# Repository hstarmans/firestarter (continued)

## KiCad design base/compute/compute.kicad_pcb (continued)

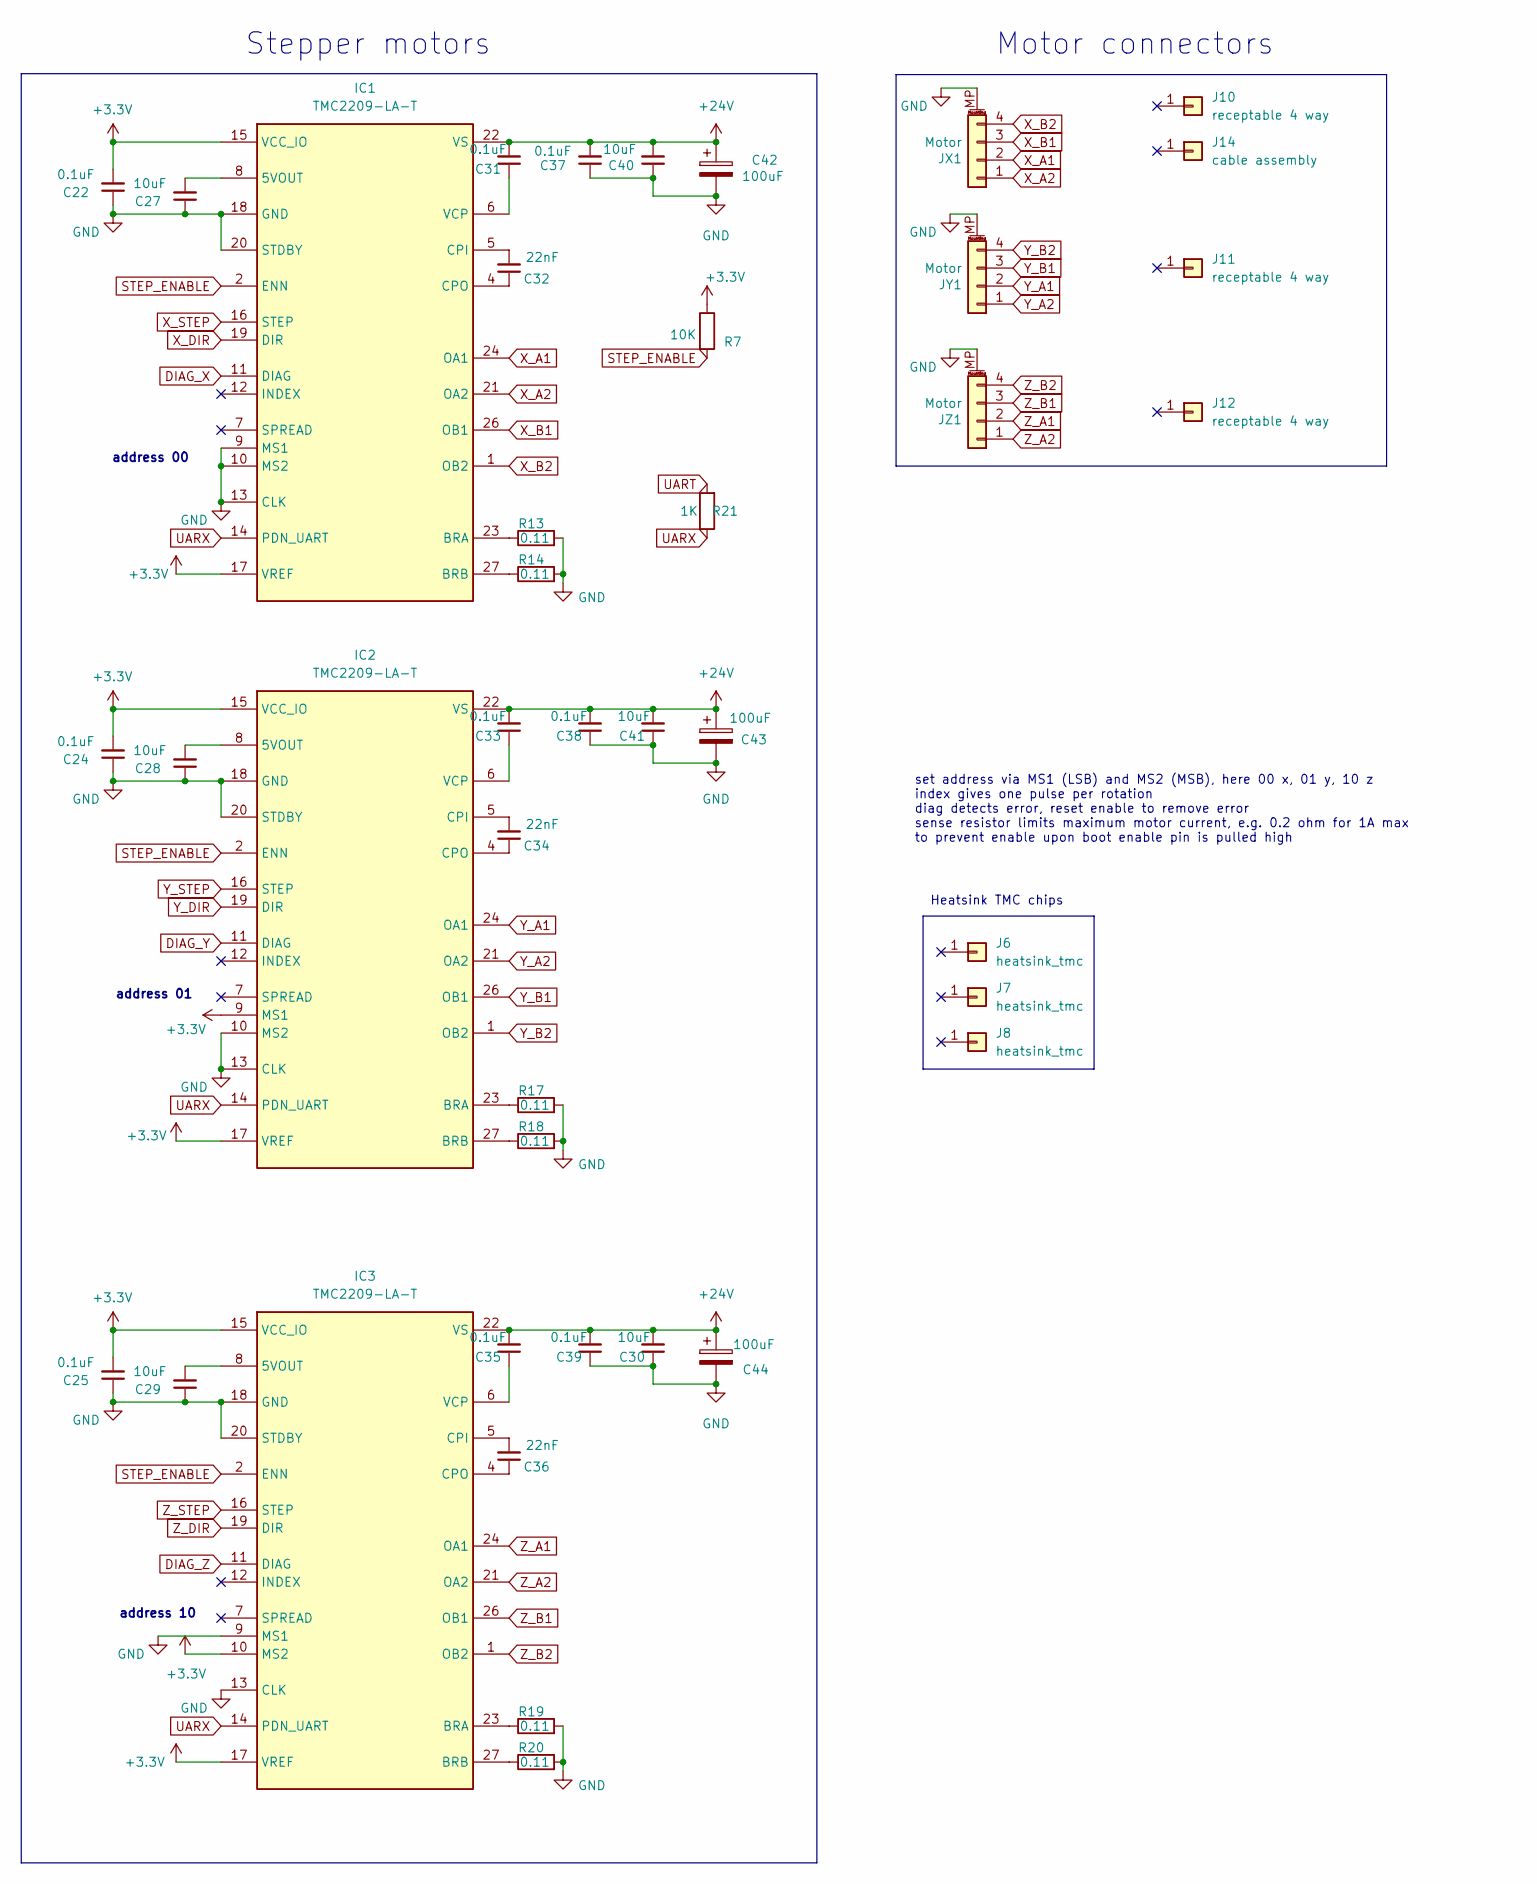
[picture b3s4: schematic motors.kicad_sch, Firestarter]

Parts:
C22, C24, C25, C31, C33, C35, C37, C38, C39: 0.1uF; C_0805_2012Metric_Pad1.18x1.45mm_HandSolder; mouser# 80-C0805C104J5R
C27, C28, C29, C30, C40, C41: 10uF; C_0805_2012Metric_Pad1.18x1.45mm_HandSolder; mouser# 81-GRM21BR61H106KE3L
C32, C34, C36: 22nF; C_0805_2012Metric_Pad1.18x1.45mm_HandSolder; mouser# 603-CC805KRX7R9BB222
C42, C43, C44: 100uF; CP_Elec_6.3x7.7; mouser# 647-UCD1V101MNL1GS; farnell# 4765491
IC1, IC2, IC3: TMC2209-LA-T; QFN50P500X500X90-29N-D; mouser# 700-TMC2209-LA-T; farnell# 3131535
J6, J7, J8: heatsink_tmc; mouser# 490-HSB01-080808
J10, J11, J12: receptable 4 way; mouser# 306-XHP-4
J14: cable assembly; mouser# 306-SXH-001T-P0.6
JX1: Motor; JST_XH_S4B-XH-SM4-TB_1x04-1MP_P2.50mm_Horizontal; mouser# 306-S4BXHSM4TBLFSN; farnell# 2399478
JY1: Motor; JST_XH_S4B-XH-SM4-TB_1x04-1MP_P2.50mm_Horizontal; mouser# 306-S4BXHSM4TBLFSN; farnell# 2399478
JZ1: Motor; JST_XH_S4B-XH-SM4-TB_1x04-1MP_P2.50mm_Horizontal; mouser# 306-S4BXHSM4TBLFSN; farnell# 2399478
R7: 10K; R_0805_2012Metric; mouser# 71-CRCW080510K0JNEAC; farnell# 2826162
R13, R14, R17, R18, R19, R20: 0.11; R_1206_3216Metric; mouser# 71-WSL1206R1100FEA; farnell# 1107360
R21: 1K; R_0805_2012Metric_Pad1.20x1.40mm_HandSolder; mouser# 71-CRCW0805-1.0K-E3

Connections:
+3.3V: C22.2, C24.2, C25.2, IC1.15 (VCC_IO), IC1.17 (VREF), IC2.9 (MS1), IC2.15 (VCC_IO), IC2.17 (VREF), IC3.10 (MS2), IC3.15 (VCC_IO), IC3.17 (VREF), R7.1; also elsewhere on the board
+24V: C30.2, C31.2, C33.2, C35.2, C37.2, C38.2, C39.2, C40.2, C41.2, C42.1, C43.1, C44.1, IC1.22 (VS), IC1.28 (VS), IC2.22 (VS), IC2.28 (VS), IC3.22 (VS), IC3.28 (VS); also elsewhere on the board
DIAG_X: IC1.11 (DIAG); also elsewhere on the board
DIAG_Y: IC2.11 (DIAG); also elsewhere on the board
DIAG_Z: IC3.11 (DIAG); also elsewhere on the board
GND: C22.1, C24.1, C25.1, C27.1, C28.1, C29.1, C30.1, C37.1, C38.1, C39.1, C40.1, C41.1, C42.2, C43.2, C44.2, IC1.3 (GND), IC1.9 (MS1), IC1.10 (MS2), IC1.13 (CLK), IC1.18 (GND), IC1.20 (STDBY), IC1.25 (GND), IC1.29 (GND), IC2.3 (GND), IC2.10 (MS2), IC2.13 (CLK), IC2.18 (GND), IC2.20 (STDBY), IC2.25 (GND), IC2.29 (GND), IC3.3 (GND), IC3.9 (MS1), IC3.13 (CLK), IC3.18 (GND), IC3.20 (STDBY), IC3.25 (GND), IC3.29 (GND), JX1.MP (MountPin), JY1.MP (MountPin), JZ1.MP (MountPin), R13.2, R14.2, R17.2, R18.2, R19.2, R20.2; also elsewhere on the board
unnamed: C27.2, IC1.8 (5VOUT)
unnamed: IC1.23 (BRA), R13.1
unnamed: IC1.27 (BRB), R14.1
unnamed: C32.2, IC1.5 (CPI)
unnamed: C32.1, IC1.4 (CPO)
unnamed: C31.1, IC1.6 (VCP)
unnamed: C28.2, IC2.8 (5VOUT)
unnamed: IC2.23 (BRA), R17.1
unnamed: IC2.27 (BRB), R18.1
unnamed: C34.2, IC2.5 (CPI)
unnamed: C34.1, IC2.4 (CPO)
unnamed: C33.1, IC2.6 (VCP)
unnamed: C29.2, IC3.8 (5VOUT)
unnamed: IC3.23 (BRA), R19.1
unnamed: IC3.27 (BRB), R20.1
unnamed: C36.2, IC3.5 (CPI)
unnamed: C36.1, IC3.4 (CPO)
unnamed: C35.1, IC3.6 (VCP)
STEP_ENABLE: IC1.2 (ENN), IC2.2 (ENN), IC3.2 (ENN), R7.2; also elsewhere on the board
UART: R21.2; also elsewhere on the board
UARX: IC1.14 (PDN_UART), IC2.14 (PDN_UART), IC3.14 (PDN_UART), R21.1; also elsewhere on the board
X_A1: IC1.24 (OA1), JX1.2
X_A2: IC1.21 (OA2), JX1.1
X_B1: IC1.26 (OB1), JX1.3
X_B2: IC1.1 (OB2), JX1.4
X_DIR: IC1.19 (DIR); also elsewhere on the board
X_STEP: IC1.16 (STEP); also elsewhere on the board
Y_A1: IC2.24 (OA1), JY1.2
Y_A2: IC2.21 (OA2), JY1.1
Y_B1: IC2.26 (OB1), JY1.3
Y_B2: IC2.1 (OB2), JY1.4
Y_DIR: IC2.19 (DIR); also elsewhere on the board
Y_STEP: IC2.16 (STEP); also elsewhere on the board
Z_A1: IC3.24 (OA1), JZ1.2
Z_A2: IC3.21 (OA2), JZ1.1
Z_B1: IC3.26 (OB1), JZ1.3
Z_B2: IC3.1 (OB2), JZ1.4
Z_DIR: IC3.19 (DIR); also elsewhere on the board
Z_STEP: IC3.16 (STEP); also elsewhere on the board

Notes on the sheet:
set address via MS1 (LSB) and MS2 (MSB), here 00 x, 01 y, 10 z index gives one pulse per rotation diag detects error, reset enable to remove error sense resistor limits maximum motor current, e.g. 0.2 ohm for 1A max to prevent enable upon boot enable pin is pulled high
address 10
address 00
Heatsink TMC chips
address 01
Stepper motors
Motor connectors

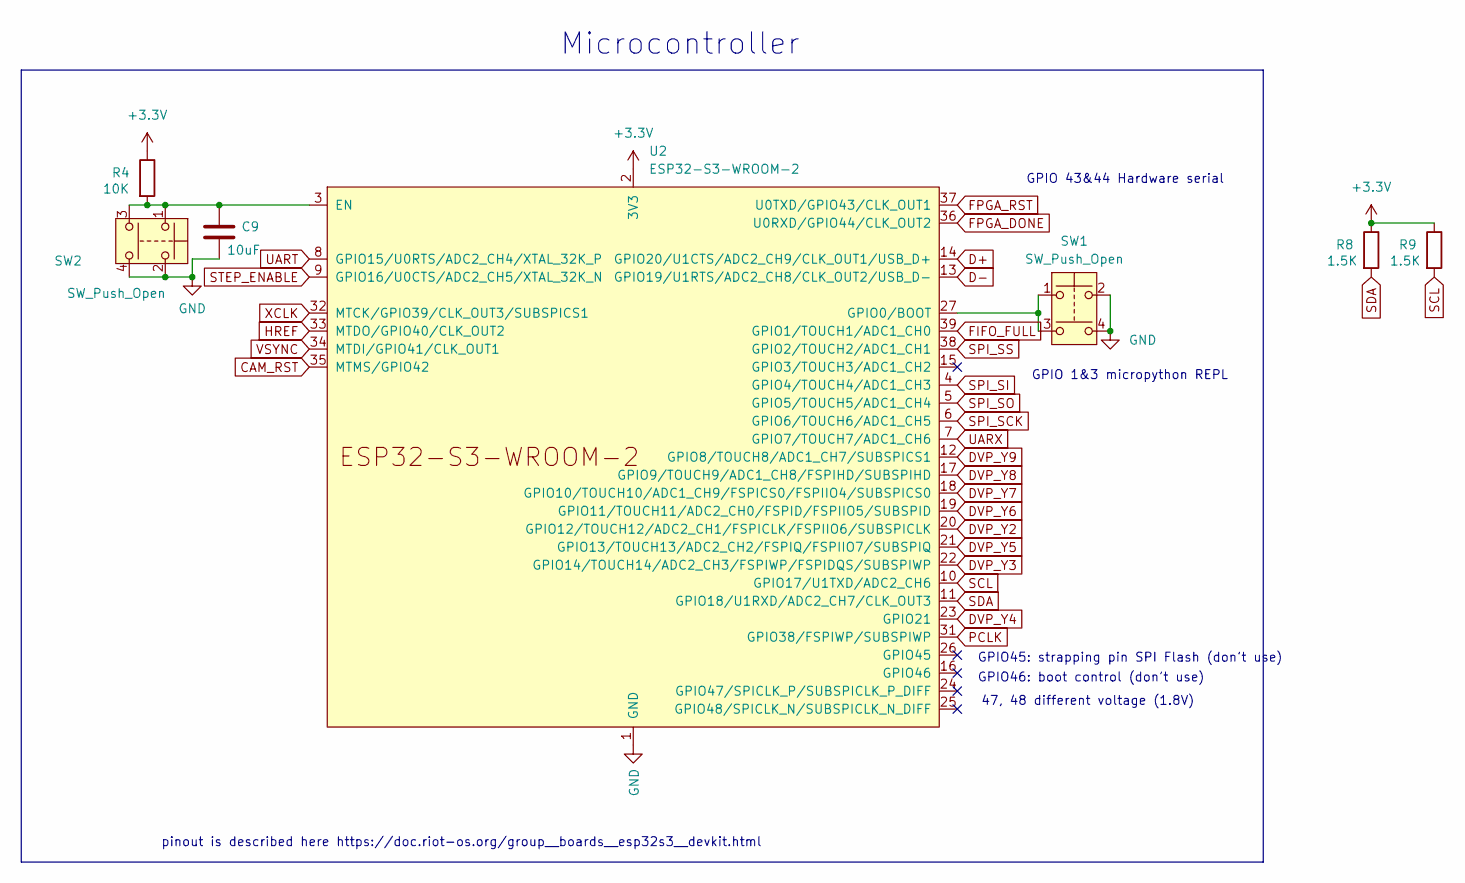
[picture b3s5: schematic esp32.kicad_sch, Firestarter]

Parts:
C9: 10uF; C_0805_2012Metric_Pad1.18x1.45mm_HandSolder; mouser# 81-GRM21BR61H106KE3L; farnell# 3790440
R4: 10K; R_0805_2012Metric; mouser# 71-CRCW080510K0JNEAC; farnell# 2826162
R8, R9: 1.5K; R_0805_2012Metric; mouser# 652-CR0805JW-152ELF; farnell# 2908429
SW1, SW2: SW_Push_Open; SKRPABE010; mouser# 688-SKRPAB; farnell# 3261824
U2: ESP32-S3-WROOM-2; mouser# 356-SP32S3WM2N32R16V

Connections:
+3.3V: R4.1, R8.1, R9.1, U2.2 (3V3); also elsewhere on the board
CAM_RST: U2.35 (MTMS/GPIO42); also elsewhere on the board
D+: U2.14 (GPIO20/U1CTS/ADC2_CH9/CLK_OUT1/USB_D+); also elsewhere on the board
D-: U2.13 (GPIO19/U1RTS/ADC2_CH8/CLK_OUT2/USB_D-); also elsewhere on the board
DVP_Y2: U2.20 (GPIO12/TOUCH12/ADC2_CH1/FSPICLK/FSPIIO6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); also elsewhere on the board
DVP_Y3: U2.22 (GPIO14/TOUCH14/ADC2_CH3/FSPIWP/FSPIDQS/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); also elsewhere on the board
DVP_Y4: U2.23 (GPIO21); also elsewhere on the board
DVP_Y5: U2.21 (GPIO13/TOUCH13/ADC2_CH2/FSPIQ/FSPIIO7/S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); also elsewhere on the board
DVP_Y6: U2.19 (GPIO11/TOUCH11/ADC2_CH0/FSPID/FSPIIO5/S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); also elsewhere on the board
DVP_Y7: U2.18 (GPIO10/TOUCH10/ADC1_CH9/FSPICS0/FSPIIO4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); also elsewhere on the board
DVP_Y8: U2.17 (GPIO9/TOUCH9/ADC1_CH8/FSPIHD/SUBSPIHD); also elsewhere on the board
DVP_Y9: U2.12 (GPIO8/TOUCH8/ADC1_CH7/SUBSPICS1); also elsewhere on the board
FIFO_FULL: U2.39 (GPIO1/TOUCH1/ADC1_CH0); also elsewhere on the board
FPGA_DONE: U2.36 (U0RXD/GPIO44/CLK_OUT2); also elsewhere on the board
FPGA_RST: U2.37 (U0TXD/GPIO43/CLK_OUT1); also elsewhere on the board
GND: C9.2, SW1.2, SW1.4, SW2.2, SW2.4, U2.1 (GND), U2.40 (GND), U2.41 (GND); also elsewhere on the board
HREF: U2.33 (MTDO/GPIO40/CLK_OUT2); also elsewhere on the board
unnamed: C9.1, R4.2, SW2.1, SW2.3, U2.3 (EN)
unnamed: SW1.1, SW1.3, U2.27 (GPIO0/BOOT)
PCLK: U2.31 (GPIO38/FSPIWP/SUBSPIWP); also elsewhere on the board
SCL: R9.2, U2.10 (GPIO17/U1TXD/ADC2_CH6); also elsewhere on the board
SDA: R8.2, U2.11 (GPIO18/U1RXD/ADC2_CH7/CLK_OUT3); also elsewhere on the board
SPI_SCK: U2.6 (GPIO6/TOUCH6/ADC1_CH5); also elsewhere on the board
SPI_SI: U2.4 (GPIO4/TOUCH4/ADC1_CH3); also elsewhere on the board
SPI_SO: U2.5 (GPIO5/TOUCH5/ADC1_CH4); also elsewhere on the board
SPI_SS: U2.38 (GPIO2/TOUCH2/ADC1_CH1); also elsewhere on the board
STEP_ENABLE: U2.9 (GPIO16/U0CTS/ADC2_CH5/XTAL_32K_N); also elsewhere on the board
UART: U2.8 (GPIO15/U0RTS/ADC2_CH4/XTAL_32K_P); also elsewhere on the board
UARX: U2.7 (GPIO7/TOUCH7/ADC1_CH6); also elsewhere on the board
VSYNC: U2.34 (MTDI/GPIO41/CLK_OUT1); also elsewhere on the board
XCLK: U2.32 (MTCK/GPIO39/CLK_OUT3/SUBSPICS1); also elsewhere on the board

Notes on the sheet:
Microcontroller
GPIO 1&3 micropython REPL
pinout is described here https://doc.riot-os.org/group__boards__esp32s3__devkit.html
GPIO45: strapping pin SPI Flash (don't use)
GPIO46: boot control (don't use)
GPIO 43&44 Hardware serial
47, 48 different voltage (1.8V)

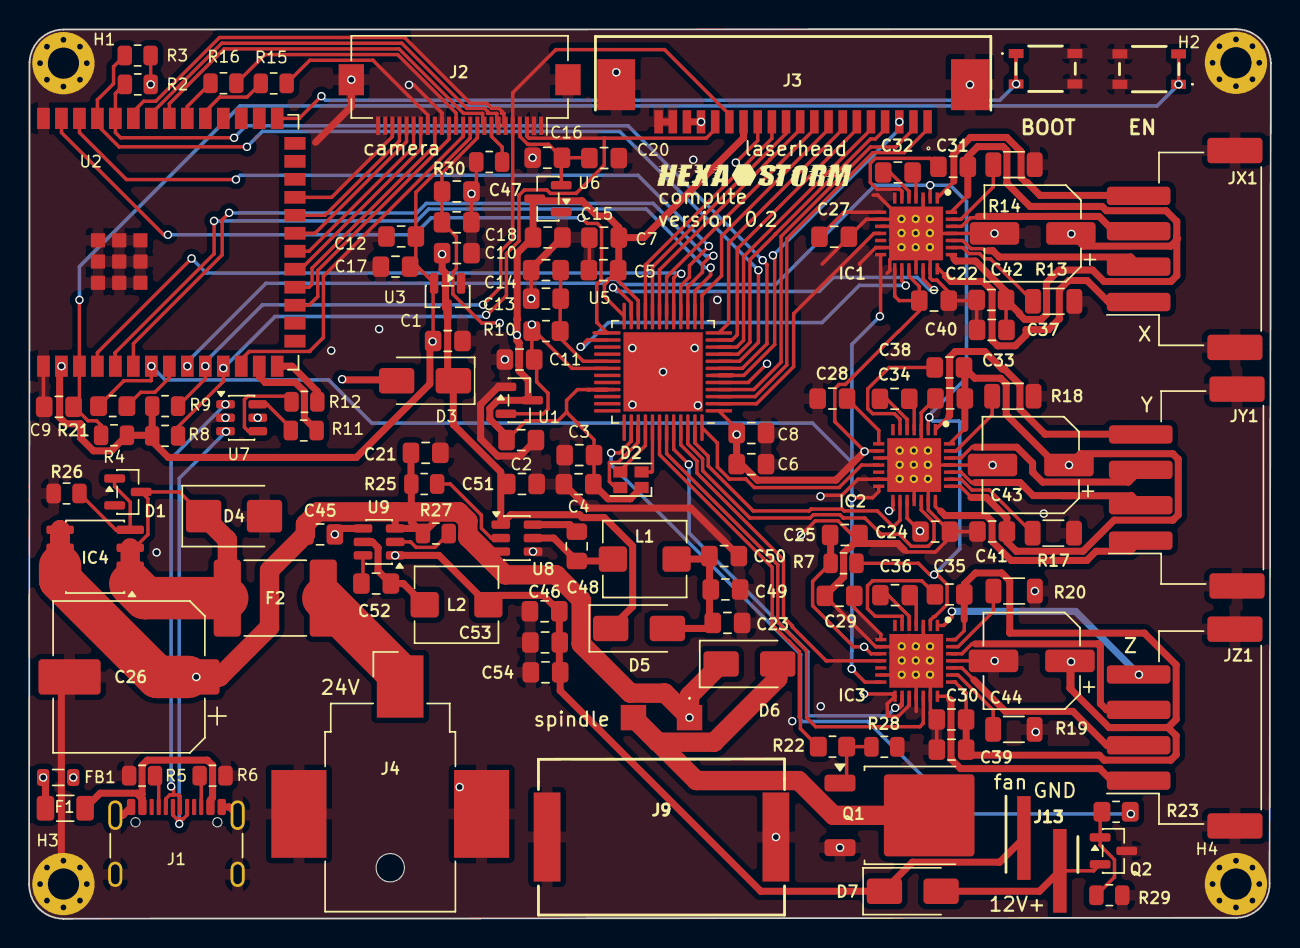
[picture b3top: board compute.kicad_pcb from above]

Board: 4 copper layers, 87.7 x 62.8 mm, 123 parts (0 on the bottom side), 119 nets.

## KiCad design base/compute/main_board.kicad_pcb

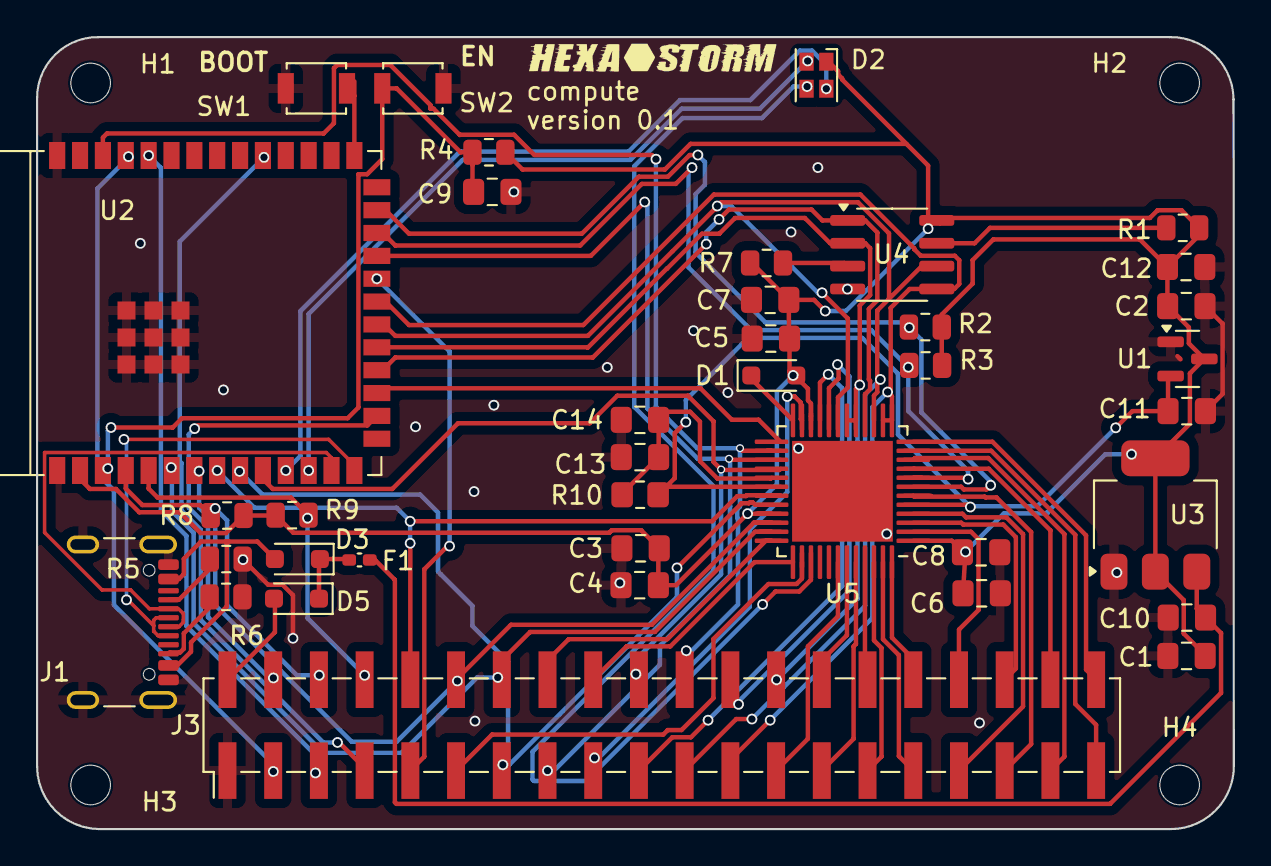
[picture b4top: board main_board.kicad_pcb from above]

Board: 2 copper layers, 66.5 x 44.0 mm, 43 parts (0 on the bottom side), 62 nets.

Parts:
C1, C2, C9, C10, C11: 1uF; C_0805_2012Metric_Pad1.18x1.45mm_HandSolder
C3, C5, C6, C12, C14: 0.1u; C_0805_2012Metric_Pad1.18x1.45mm_HandSolder
C4, C7, C8, C13: 4.7u; C_0805_2012Metric_Pad1.18x1.45mm_HandSolder
D1, D3, D5: D_Schottky; D_SOD-323_HandSoldering
D2: LED_ABGR; LED_Cree-PLCC4_2x2mm_CW
F1: Fuse; Fuse_0402_1005Metric_Pad0.77x0.64mm_HandSolder
G1: hexastorm
H1, H2, H3, H4: MountingHole; MountingHole_2.2mm_M2
J1: USB_C_Receptacle_USB2.0_16P; USB_C_Receptacle_GCT_USB4105-xx-A_16P_TopMnt_Horizontal
J3: Conn_02x20_Counter_Clockwise; PinHeader_2x20_P2.54mm_Vertical_SMD
R1, R2, R3, R4, R7, R8, R9: 10K; R_0805_2012Metric
R5, R6: 5.1K; R_0805_2012Metric
R10: 100; R_0805_2012Metric_Pad1.20x1.40mm_HandSolder
SW1, SW2: SW_Push_Open; SW_SPST_B3U-1000P
U1: MCP1700T-1202ETT; SOT-23
U2: ESP32-S3-WROOM-2
U3: LD1117S33TR_SOT223; SOT-223-3_TabPin2
U4: W25X20CLSN; SOIC-8_3.9x4.9mm_P1.27mm
U5: ICE40UP5K-SG48ITR-FPGA_Lattice; QFN-48-1EP_7x7mm_P0.5mm_EP5.6x5.6mm

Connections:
5Vfuse: D3.1 (K), D5.1 (K), F1.1
+1V2: C11.1, R10.1, U1.2 (VO), U5.5 (VCC), U5.30 (VCC)
+3.3V: C1.1, C2.1, C3.1, C4.1, C5.1, C6.1, C7.1, C8.1, C12.1, D1.2 (A), D2.1 (A), R1.1, R2.1, R3.2, R4.1, R7.1, R8.1, R9.1, U1.3 (VI), U2.2 (3V3), U3.2 (VO), U4.8 (VCC), U5.1 (VCCIO_2), U5.22 (SPI_VCCIO1), U5.33 (VCCIO_0)
+5V: C10.1, F1.2, U3.3 (VI)
CFG_DONE: R2.2, U2.25 (GPIO48/SPICLK_N/SUBSPICLK_N_DIFF), U5.7 (CDONE)
CFG_RST: R3.1, U2.24 (GPIO47/SPICLK_P/SUBSPICLK_P_DIFF), U5.8 (~CRESET)
D+: J1.A6 (D+), J1.B6 (D+), U2.14 (GPIO20/U1CTS/ADC2_CH9/CLK_OUT1/USB_D+)
D-: J1.A7 (D-), J1.B7 (D-), U2.13 (GPIO19/U1RTS/ADC2_CH8/CLK_OUT2/USB_D-)
DIGITAL: J3.29, U5.46 (IOB_0a)
ESP32_BLUE: D2.2 (BK), U2.11 (GPIO18/U1RXD/ADC2_CH7/CLK_OUT3)
ESP32_RED: D2.4 (RK), U2.12 (GPIO8/TOUCH8/ADC1_CH7/SUBSPICS1)
FPGA3: J3.27, U5.44 (IOB_3b_G6)
FPGA42: J3.10, U2.8 (GPIO15/U0RTS/ADC2_CH4/XTAL_32K_P), U5.31 (IOT_42b)
FPGA43: J3.13, U2.9 (GPIO16/U0CTS/ADC2_CH5/XTAL_32K_N), U5.32 (IOT_43a)
FPGA44: J3.12, U2.7 (GPIO7/TOUCH7/ADC1_CH6), U5.34 (IOT_44b)
FPGA49: J3.28, U5.43 (IOT_49a)
FPGA50: J3.11, U5.38 (IOT_50b)
FPGAG: D2.3 (GK), U5.39 (RGB0)
GND: C1.2, C2.2, C3.2, C4.2, C5.2, C6.2, C7.2, C8.2, C9.2, C10.2, C11.2, C12.2, C13.1, C14.1, J1.A1 (GND), J1.A12 (GND), J1.B1 (GND), J1.B12 (GND), J1.S1 (SHIELD), J3.1, R5.2, R6.2, SW1.2, SW2.2, U1.1 (GND), U2.1 (GND), U2.40 (GND), U2.41 (GND), U3.1 (GND), U4.4 (GND), U5.49 (GND)
GPIO14: J3.9, U2.22 (GPIO14/TOUCH14/ADC2_CH3/FSPIWP/FSPIDQS/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)
GPIO46: J3.4, U2.16 (GPIO46)
HALL1: J3.30, U5.45 (IOB_5b)
HALL2: J3.31, U5.47 (IOB_2a)
HALL3: J3.32, U5.48 (IOB_4a)
IC_HB_PWM1: J3.39, U5.11 (IOB_20a)
IC_HB_PWM2: J3.40, U5.12 (IOB_22a)
INDEX_X: J3.20, U2.10 (GPIO17/U1TXD/ADC2_CH6), U5.28 (IOT_41a)
unnamed: D1.1 (K), U5.24 (VPP_2V5)
unnamed: D3.2 (A), J1.A4 (VBUS), J1.A9 (VBUS), J1.B4 (VBUS), J1.B9 (VBUS)
unnamed: D5.2 (A), J3.2
unnamed: J1.A5 (CC1), R5.1
unnamed: J1.B5 (CC2), R6.1
unnamed: C9.1, R4.2, SW2.1, U2.3 (EN)
unnamed: SW1.1, U2.27 (GPIO0/BOOT)
unnamed: R1.2, U4.7 (~HOLD)
unnamed: R7.2, U4.3 (~WP)
unnamed: C13.2, C14.2, R10.2, U5.29 (VCCPLL)
POT_SCL: J3.8, R9.2, U2.5 (GPIO5/TOUCH5/ADC1_CH4)
POT_SDA: J3.6, R8.2, U2.4 (GPIO4/TOUCH4/ADC1_CH3)
SPI_SCK: J3.21, U2.20 (GPIO12/TOUCH12/ADC2_CH1/FSPICLK/FSPIIO6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), U4.6 (SCK), U5.15 (IOB_34a_SPI_SCK), U5.19 (IOB_29b)
SPI_SI: J3.26, U2.19 (GPIO11/TOUCH11/ADC2_CH0/FSPID/FSPIIO5/S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), U4.2 (DO(IO1)), U5.17 (IOB_33b_SPI_SI), U5.18 (IOB_31b)
SPI_SO: J3.23, U2.21 (GPIO13/TOUCH13/ADC2_CH2/FSPIQ/FSPIIO7/S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), U4.5 (DI(IO0)), U5.13 (IOB_24a), U5.14 (IOB_32a_SPI_SO)
SPI_SS: U2.18 (GPIO10/TOUCH10/ADC1_CH9/FSPICS0/FSPIIO4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), U4.1 (~CS), U5.16 (IOB_35b_SPI_SS)
SPI_SS_FPGA: U2.17 (GPIO9/TOUCH9/ADC1_CH8/FSPIHD/SUBSPIHD), U5.25 (IOT_36b)
STEP_ENABLE: J3.7, U2.31 (GPIO38/FSPIWP/SUBSPIWP)
UART: J3.3, U2.37 (U0TXD/GPIO43/CLK_OUT1)
UARX: J3.5, U2.36 (U0RXD/GPIO44/CLK_OUT2)
X_DIR: J3.24, U5.20 (IOB_25b_G3)
X_PO: J3.25, U5.42 (IOT_51a)
X_STEP: J3.22, U2.38 (GPIO2/TOUCH2/ADC1_CH1), U5.26 (IOT_39a)
Y_DIR: J3.16, U5.36 (IOT_48b)
Y_PO: J3.19, U5.21 (IOB_23b)
Y_STEP: J3.18, U5.37 (IOT_45a_G1)
Z_DIR: J3.15, U2.23 (GPIO21), U5.27 (IOT_38b)
Z_PO: J3.17, U5.23 (IOT_37a)
Z_STEP: J3.14, U2.6 (GPIO6/TOUCH6/ADC1_CH5), U5.35 (IOT_46b_G0)
uH: J3.33, U5.4 (IOB_8a)
uL: J3.34, U5.2 (IOB_6a)
vH: J3.35, U5.6 (IOB_13b)
vL: J3.36, U5.3 (IOB_9b)
wH: J3.37, U5.10 (IOB_18a)
wL: J3.38, U5.9 (IOB_16a)

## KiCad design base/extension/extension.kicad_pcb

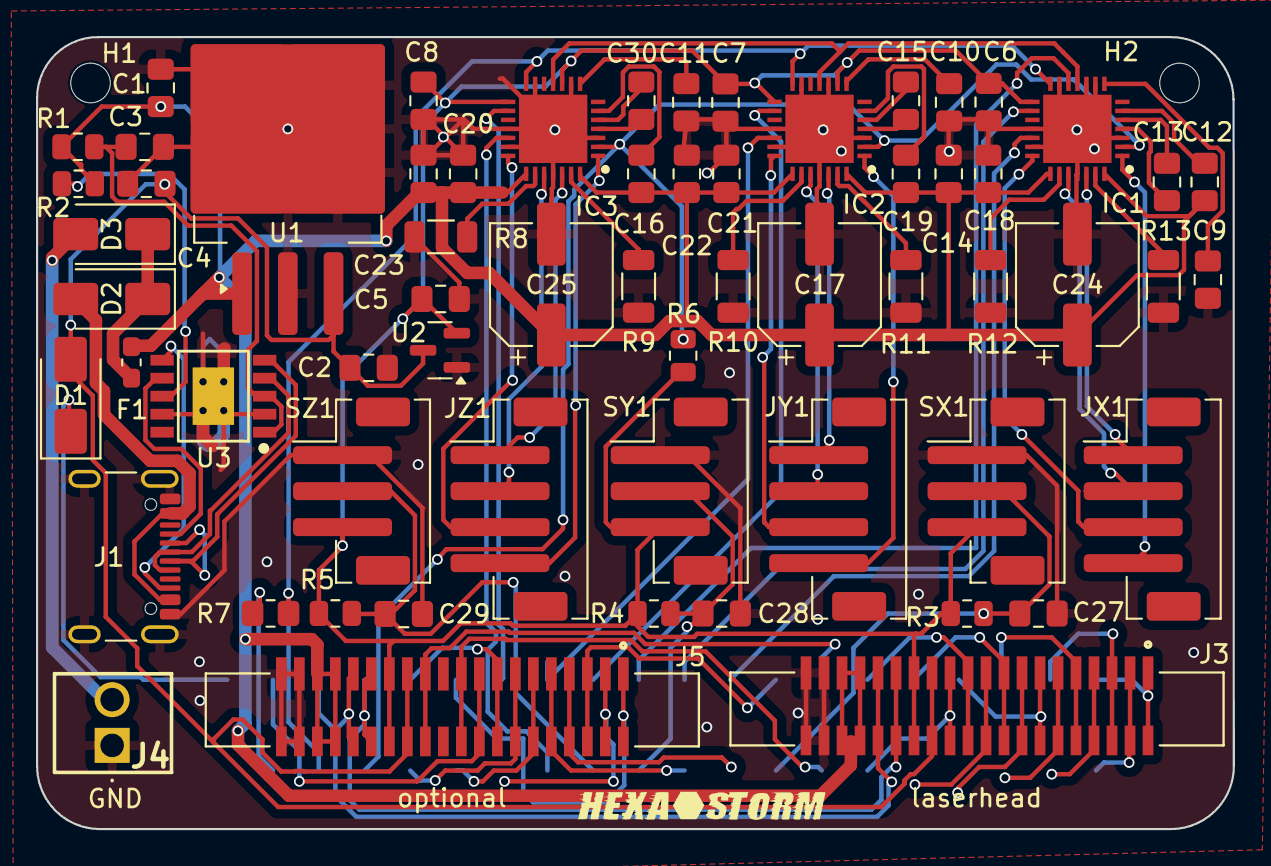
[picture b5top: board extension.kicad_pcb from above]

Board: 2 copper layers, 66.5 x 44.0 mm, 66 parts (1 on the bottom side), 83 nets.

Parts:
C1, C2, C3, C5: 1uF; C_0805_2012Metric_Pad1.18x1.45mm_HandSolder
C4, C6, C7, C8, C12, C14, C16, C18, C19, C20, C21, C22, C23, C27, C28, C29: 0.1uF; C_0805_2012Metric_Pad1.18x1.45mm_HandSolder
C9, C10, C11: 4.7uF; C_0805_2012Metric_Pad1.18x1.45mm_HandSolder
C13, C15, C30: 22nF; C_0805_2012Metric_Pad1.18x1.45mm_HandSolder
C17, C24, C25: 100uF; CP_Elec_6.3x5.4
D1, D2, D3: D_Schottky; D_SMA
F1: Fuse; Fuse_0603_1608Metric_Pad1.05x0.95mm_HandSolder
G1: hexastorm
H1, H2: MountingHole; MountingHole_2.2mm_M2
IC1, IC2, IC3: TMC2209-LA-T; QFN50P500X500X90-29N-D
J1: USB_C_Receptacle_USB2.0_16P; USB_C_Receptacle_GCT_USB4105-xx-A_16P_TopMnt_Horizontal
J2: Conn_02x20_Odd_Even; PinSocket_2x20_P2.54mm_Vertical_SMD
J3, J5: 2-1734248-0; TE_2-1734248-0
J4: Conn_01x02; VN02A1500000G
JX1: X; JST_PH_B4B-PH-SM4-TB_1x04-1MP_P2.00mm_Vertical
JY1: Y; JST_PH_B4B-PH-SM4-TB_1x04-1MP_P2.00mm_Vertical
JZ1: Z; JST_PH_B4B-PH-SM4-TB_1x04-1MP_P2.00mm_Vertical
R1: 1K; R_0805_2012Metric
R2, R3, R4, R5, R6: 10K; R_0805_2012Metric
R7: 1K; R_0805_2012Metric_Pad1.20x1.40mm_HandSolder
R8, R9, R10, R11, R12, R13: 0.5; R_1206_3216Metric
SX1: X; JST_PH_B3B-PH-SM4-TB_1x03-1MP_P2.00mm_Vertical
SY1: Y; JST_PH_B3B-PH-SM4-TB_1x03-1MP_P2.00mm_Vertical
SZ1: Z; JST_PH_B3B-PH-SM4-TB_1x03-1MP_P2.00mm_Vertical
U1: LM7805_TO263; TO-263-3_TabPin2
U2: MCP1700T-3302E/TT; SOT-23
U3: CH224K; ESSOP-10_CH224K

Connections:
+3.3V: C5.2, C6.2, C7.2, C8.2, IC1.15 (VCC_IO), IC2.9 (MS1), IC2.15 (VCC_IO), IC3.10 (MS2), IC3.15 (VCC_IO), J3.14, J3.14_1 (14), J5.14, J5.14_1 (14), R3.1, R4.1, R5.1, R6.1, SX1.3, SY1.3, SZ1.3, U2.2 (VO)
+5V: C2.2, C4.1, D1.2 (A), J3.13, J3.13_1 (13), J5.13, J5.13_1 (13), U1.3 (VO), U2.3 (VI)
+12V: C1.1, C12.2, C14.2, C16.2, C17.1, C18.2, C19.2, C20.2, C21.2, C22.2, C23.2, C24.1, C25.1, F1.2, IC1.22 (VS), IC1.28 (VS), IC2.22 (VS), IC2.28 (VS), IC3.22 (VS), IC3.28 (VS), J3.17, J3.17_1 (17), J3.18, J3.18_1 (18), J5.17, J5.17_1 (17), J5.18, J5.18_1 (18), R1.2, R2.1, U1.1 (VI)
CC1: J1.A5 (CC1), U3.7 (CC1)
CC2: J1.B5 (CC2), U3.6 (CC2)
DIAG: IC1.11 (DIAG), IC2.11 (DIAG), IC3.11 (DIAG)
DIGITAL: J2.29, J3.12, J3.12_1 (12)
DM: J1.A7 (D-), J1.B7 (D-), U3.5 (DM)
DP: J1.A6 (D+), J1.B6 (D+), U3.4 (DP)
FPGA3: J2.27, J5.10, J5.10_1 (10)
FPGA42: J2.10, J5.8, J5.8_1 (8)
FPGA43: J2.13, J5.2, J5.2_1 (2)
FPGA44: J2.12, J5.1, J5.1_1 (1)
FPGA49: J2.28, J5.12, J5.12_1 (12)
FPGA50: J2.11, J5.6, J5.6_1 (6)
GND: C1.2, C2.1, C3.2, C4.2, C5.1, C6.1, C7.1, C8.1, C9.1, C10.1, C11.1, C14.1, C17.2, C18.1, C20.1, C21.1, C22.1, C23.1, C24.2, C25.2, C27.2, C28.2, C29.2, IC1.3 (GND), IC1.9 (MS1), IC1.10 (MS2), IC1.13 (CLK), IC1.18 (GND), IC1.20 (STDBY), IC1.25 (GND), IC1.29 (GND), IC2.3 (GND), IC2.10 (MS2), IC2.13 (CLK), IC2.18 (GND), IC2.20 (STDBY), IC2.25 (GND), IC2.29 (GND), IC3.3 (GND), IC3.9 (MS1), IC3.13 (CLK), IC3.18 (GND), IC3.20 (STDBY), IC3.25 (GND), IC3.29 (GND), J1.A1 (GND), J1.A12 (GND), J1.B1 (GND), J1.B12 (GND), J1.S1 (SHIELD), J2.1, J3.19, J3.19_1 (19), J3.20, J3.20_1 (20), J4.1, J5.19, J5.19_1 (19), J5.20, J5.20_1 (20), R8.2, R9.2, R10.2, R11.2, R12.2, R13.2, SX1.1, SY1.1, SZ1.1, U1.2 (GND), U2.1 (GND), U3.0 (GND), U3.2 (CFG2), U3.9 (CFG1)
GPIO14: J2.9, J5.7, J5.7_1 (7)
GPIO46: J2.4, J5.9, J5.9_1 (9)
HALL1: J2.30, J3.11, J3.11_1 (11)
HALL2: J2.31, J3.10, J3.10_1 (10)
HALL3: J2.32, J3.9, J3.9_1 (9)
IC_HB_PWM1: J2.39, J3.2, J3.2_1 (2)
IC_HB_PWM2: J2.40, J3.1, J3.1_1 (1)
INDEX_X: IC1.12 (INDEX), J2.20
unnamed: D1.1 (K), J2.2
unnamed: D2.2 (A), J1.A4 (VBUS), J1.A9 (VBUS), J1.B4 (VBUS), J1.B9 (VBUS)
unnamed: D3.2 (A), J4.2
unnamed: C9.2, IC1.8 (5VOUT)
unnamed: IC1.23 (BRA), R12.1
unnamed: IC1.27 (BRB), R13.1
unnamed: C13.2, IC1.5 (CPI)
unnamed: C13.1, IC1.4 (CPO)
unnamed: C12.1, IC1.6 (VCP)
unnamed: C10.2, IC2.8 (5VOUT)
unnamed: IC2.23 (BRA), R10.1
unnamed: IC2.27 (BRB), R11.1
unnamed: C15.2, IC2.5 (CPI)
unnamed: C15.1, IC2.4 (CPO)
unnamed: C19.1, IC2.6 (VCP)
unnamed: C11.2, IC3.8 (5VOUT)
unnamed: IC3.23 (BRA), R8.1
unnamed: IC3.27 (BRB), R9.1
unnamed: C30.2, IC3.5 (CPI)
unnamed: C30.1, IC3.4 (CPO)
unnamed: C16.1, IC3.6 (VCP)
unnamed: R2.2, U3.8 (VBUS)
POT_SCL: J2.8, J3.15, J3.15_1 (15), J5.15, J5.15_1 (15)
POT_SDA: J2.6, J3.16, J3.16_1 (16), J5.16, J5.16_1 (16)
SPI_SCK: J2.21, J5.5, J5.5_1 (5)
SPI_SI: J2.26, J5.3, J5.3_1 (3)
SPI_SO: J2.23, J5.4, J5.4_1 (4)
STEP_ENABLE: IC1.2 (ENN), IC2.2 (ENN), IC3.2 (ENN), J2.7, R6.2
UART: J2.3, R7.2
UARX: IC1.14 (PDN_UART), IC2.14 (PDN_UART), IC3.14 (PDN_UART), J2.5, R7.1
VBUS: D2.1 (K), D3.1 (K), F1.1
VDD: C3.1, R1.1, U3.1 (VDD), U3.3 (CFG3)
X_A1: IC1.24 (OA1), JX1.2
X_A2: IC1.21 (OA2), JX1.3
X_B1: IC1.26 (OB1), JX1.1
X_B2: IC1.1 (OB2), JX1.4
X_DIR: IC1.19 (DIR), J2.24
X_PO: C27.1, J2.25, R3.2, SX1.2
X_STEP: IC1.16 (STEP), J2.22
Y_A1: IC2.24 (OA1), JY1.2
Y_A2: IC2.21 (OA2), JY1.3
Y_B1: IC2.26 (OB1), JY1.1
Y_B2: IC2.1 (OB2), JY1.4
Y_DIR: IC2.19 (DIR), J2.16
Y_PO: C28.1, J2.19, R4.2, SY1.2
Y_STEP: IC2.16 (STEP), J2.18
Z_A1: IC3.24 (OA1), JZ1.2
Z_A2: IC3.21 (OA2), JZ1.3
Z_B1: IC3.26 (OB1), JZ1.1
Z_B2: IC3.1 (OB2), JZ1.4
Z_DIR: IC3.19 (DIR), J2.15
Z_PO: C29.1, J2.17, R5.2, SZ1.2
Z_STEP: IC3.16 (STEP), J2.14
uH: J2.33, J3.8, J3.8_1 (8)
uL: J2.34, J3.7, J3.7_1 (7)
vH: J2.35, J3.6, J3.6_1 (6)
vL: J2.36, J3.5, J3.5_1 (5)
wH: J2.37, J3.4, J3.4_1 (4)
wL: J2.38, J3.3, J3.3_1 (3)
